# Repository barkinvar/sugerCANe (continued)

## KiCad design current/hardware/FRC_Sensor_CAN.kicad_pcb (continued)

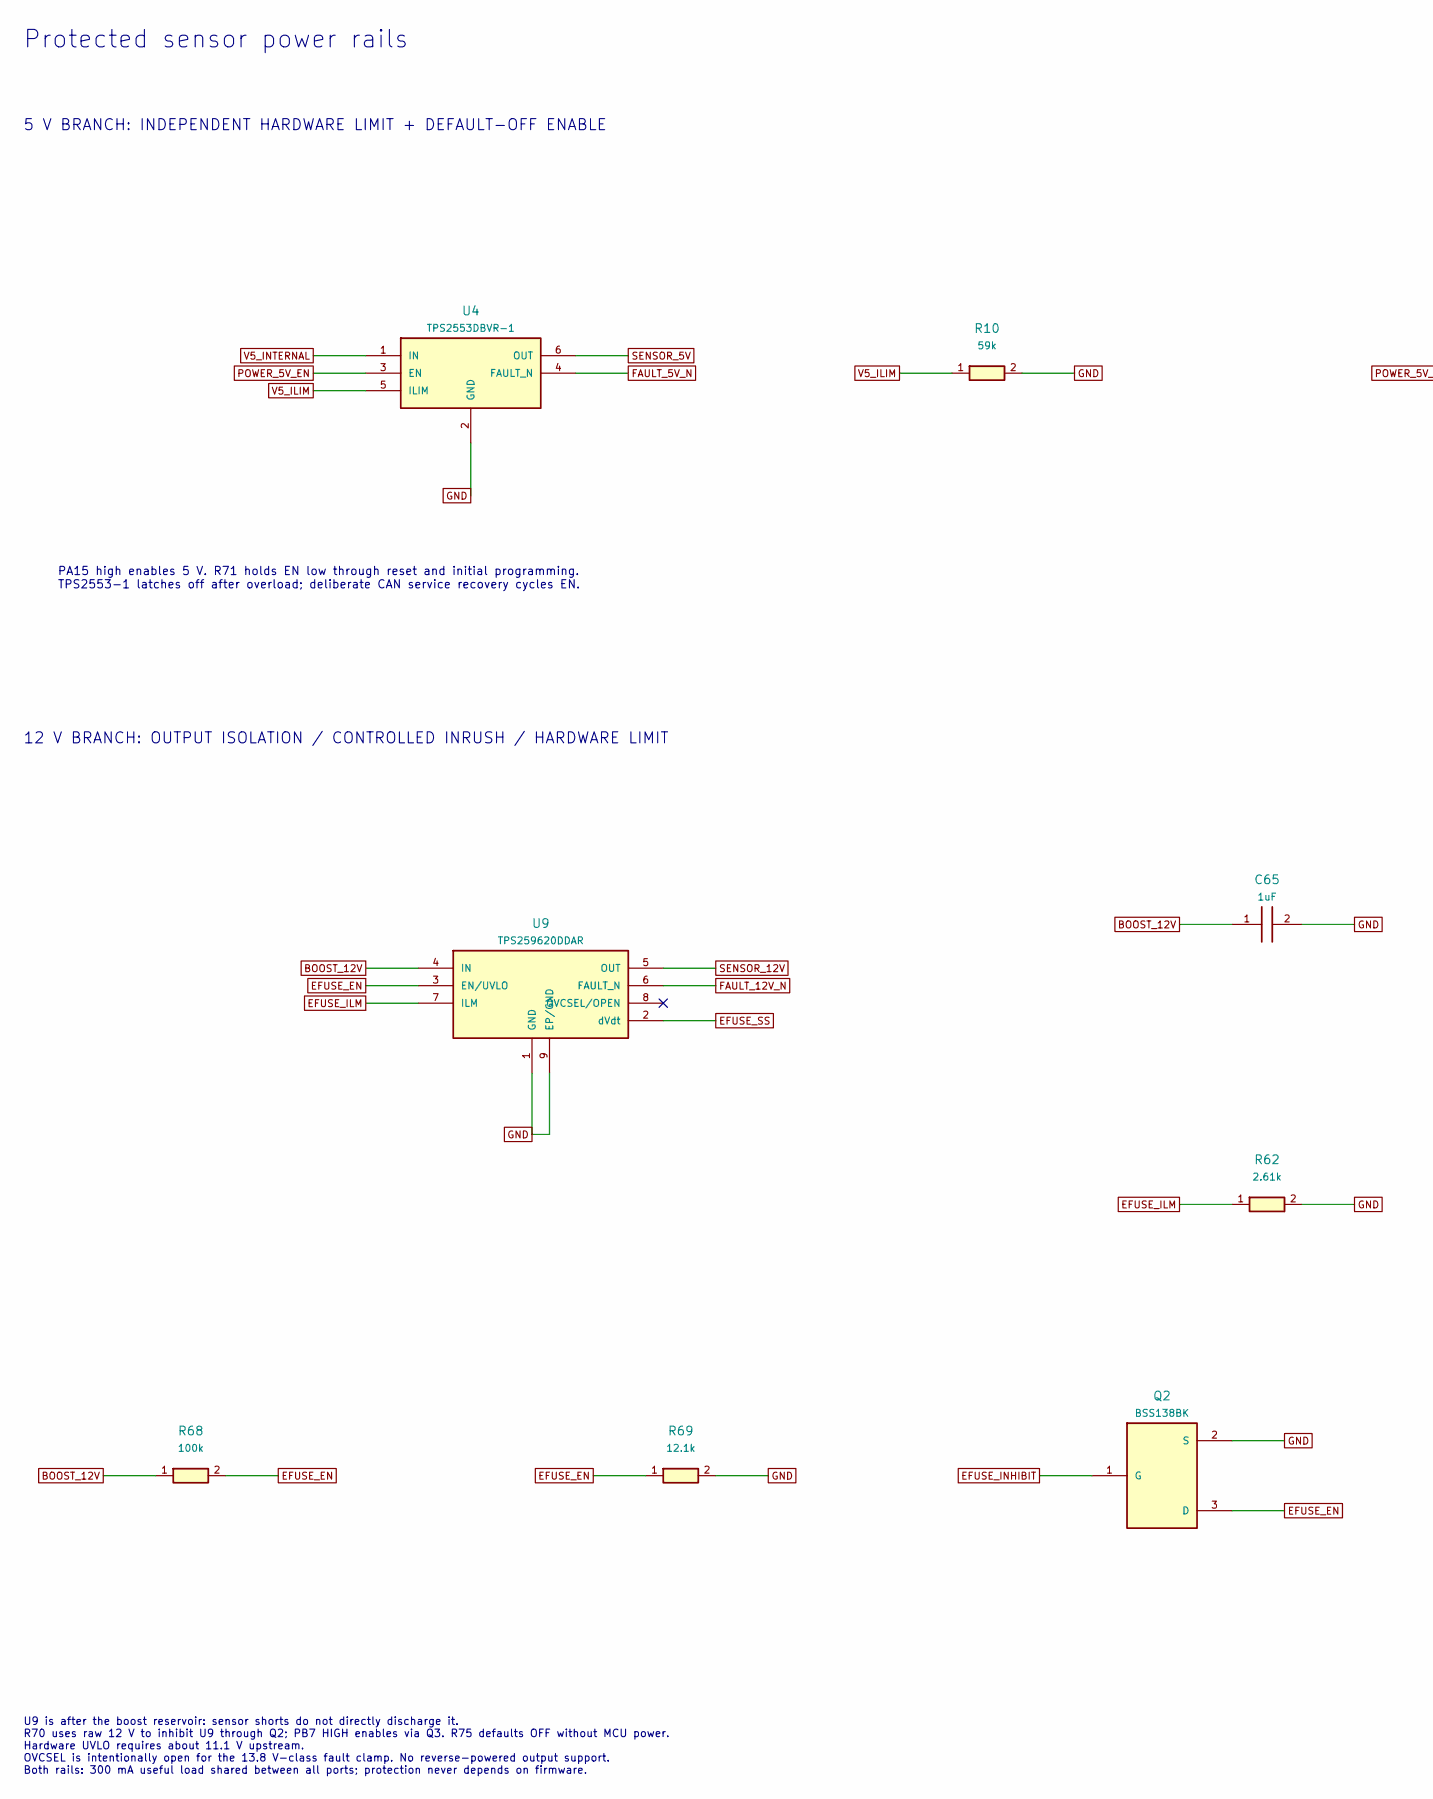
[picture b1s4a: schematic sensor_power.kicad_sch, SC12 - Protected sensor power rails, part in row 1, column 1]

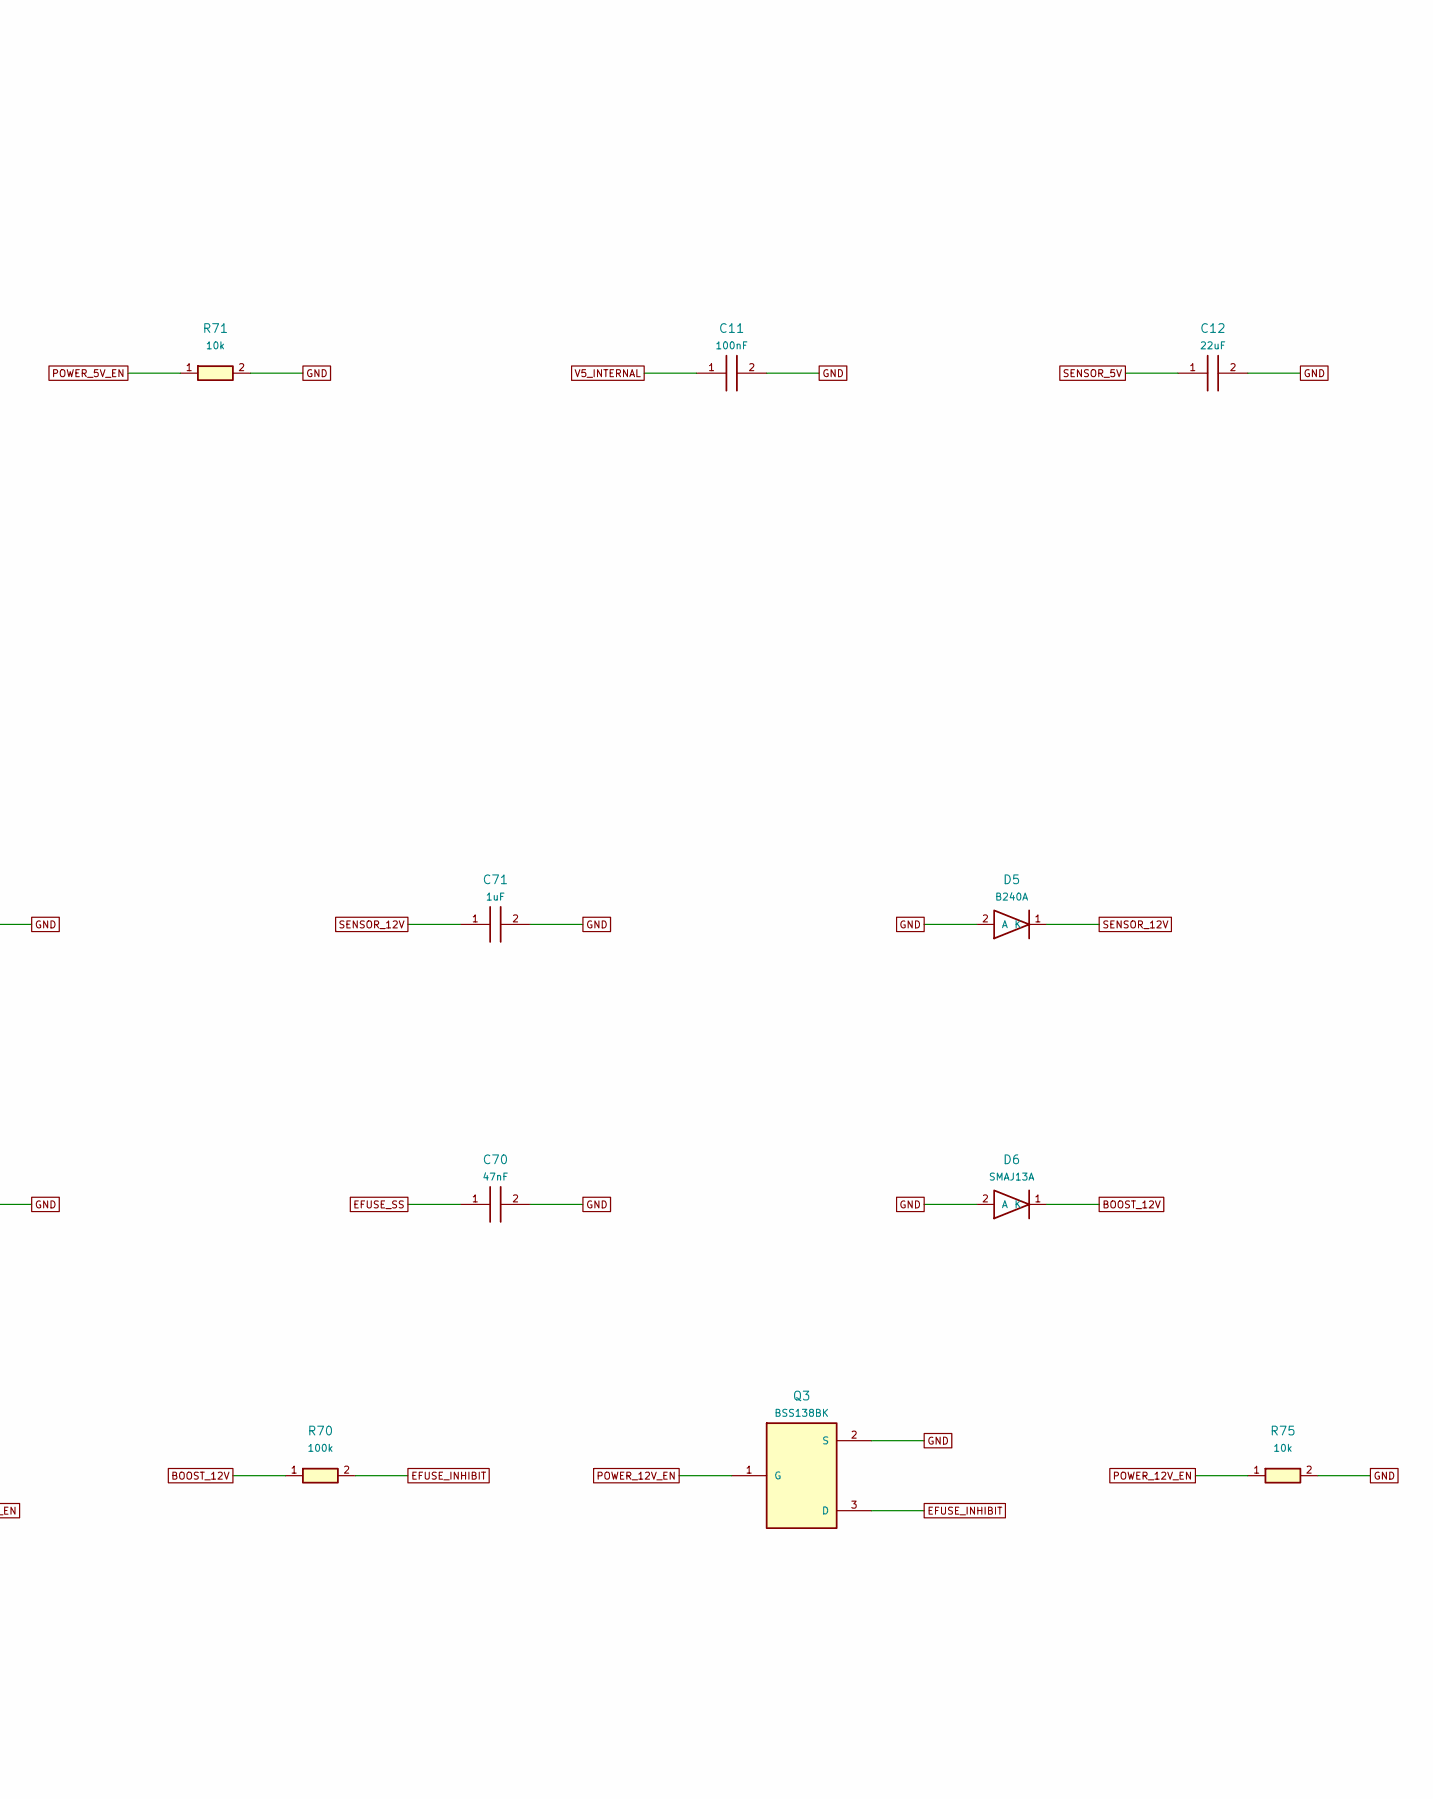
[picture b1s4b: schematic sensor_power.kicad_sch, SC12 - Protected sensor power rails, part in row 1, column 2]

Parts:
C11: 100nF; C_0805_2012Metric; MPN CL21B104KCFNNNE
C12: 22uF; C_1206_3216Metric; MPN CL31A226KAHNNNE
C65, C71: 1uF; C_0805_2012Metric; MPN CL21B105KBFNNNE
C70: 47nF; C_0805_2012Metric; MPN CL21B473KBCNNNC
D5: B240A; D_SMA; MPN B240A-13-F
D6: SMAJ13A; D_SMA; MPN SMAJ13A-13-F
Q2, Q3: BSS138BK; SOT-23; MPN BSS138BK,215
R10: 59k; R_0805_2012Metric; MPN 0805W8F5902T5E
R62: 2.61k; R_0805_2012Metric; MPN RC0805FR-072K61L
R68: 100k; R_0805_2012Metric; MPN RT0805BRD07100KL
R69: 12.1k; R_0805_2012Metric; MPN RT0805BRD0712K1L
R70: 100k; R_0805_2012Metric; MPN 0805W8F1003T5E
R71, R75: 10k; R_0805_2012Metric; MPN 0805W8F1002T5E
U4: TPS2553DBVR-1; SOT-23-6; MPN TPS2553DBVR-1
U9: TPS259620DDAR; TPS2596_DDA8; MPN TPS259620DDAR

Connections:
BOOST_12V: C65.1, D6.1 (K), R68.1, R70.1, U9.4 (IN); also elsewhere on the board
EFUSE_EN: Q2.3 (D), R68.2, R69.1, U9.3 (EN/UVLO)
EFUSE_ILM: R62.1, U9.7 (ILM)
EFUSE_INHIBIT: Q2.1 (G), Q3.3 (D), R70.2
EFUSE_SS: C70.1, U9.2 (dVdt)
FAULT_5V_N: U4.4 (FAULT_N); also elsewhere on the board
FAULT_12V_N: U9.6 (FAULT_N); also elsewhere on the board
GND: C11.2, C12.2, C65.2, C70.2, C71.2, D5.2 (A), D6.2 (A), Q2.2 (S), Q3.2 (S), R10.2, R62.2, R69.2, R71.2, R75.2, U4.2 (GND), U9.1 (GND), U9.9 (EP/GND); also elsewhere on the board
POWER_5V_EN: R71.1, U4.3 (EN); also elsewhere on the board
POWER_12V_EN: Q3.1 (G), R75.1; also elsewhere on the board
SENSOR_5V: C12.1, U4.6 (OUT); also elsewhere on the board
SENSOR_12V: C71.1, D5.1 (K), U9.5 (OUT); also elsewhere on the board
V5_ILIM: R10.1, U4.5 (ILIM)
V5_INTERNAL: C11.1, U4.1 (IN); also elsewhere on the board

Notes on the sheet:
Protected sensor power rails
5 V BRANCH: INDEPENDENT HARDWARE LIMIT + DEFAULT-OFF ENABLE
PA15 high enables 5 V. R71 holds EN low through reset and initial programming. TPS2553-1 latches off after overload; deliberate CAN service recovery cycles EN.
12 V BRANCH: OUTPUT ISOLATION / CONTROLLED INRUSH / HARDWARE LIMIT
U9 is after the boost reservoir: sensor shorts do not directly discharge it. R70 uses raw 12 V to inhibit U9 through Q2; PB7 HIGH enables via Q3. R75 defaults OFF without MCU power. Hardware UVLO requires about 11.1 V upstream. OVCSEL is intentionally open for the 13.8 V-class fault clamp. No rever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

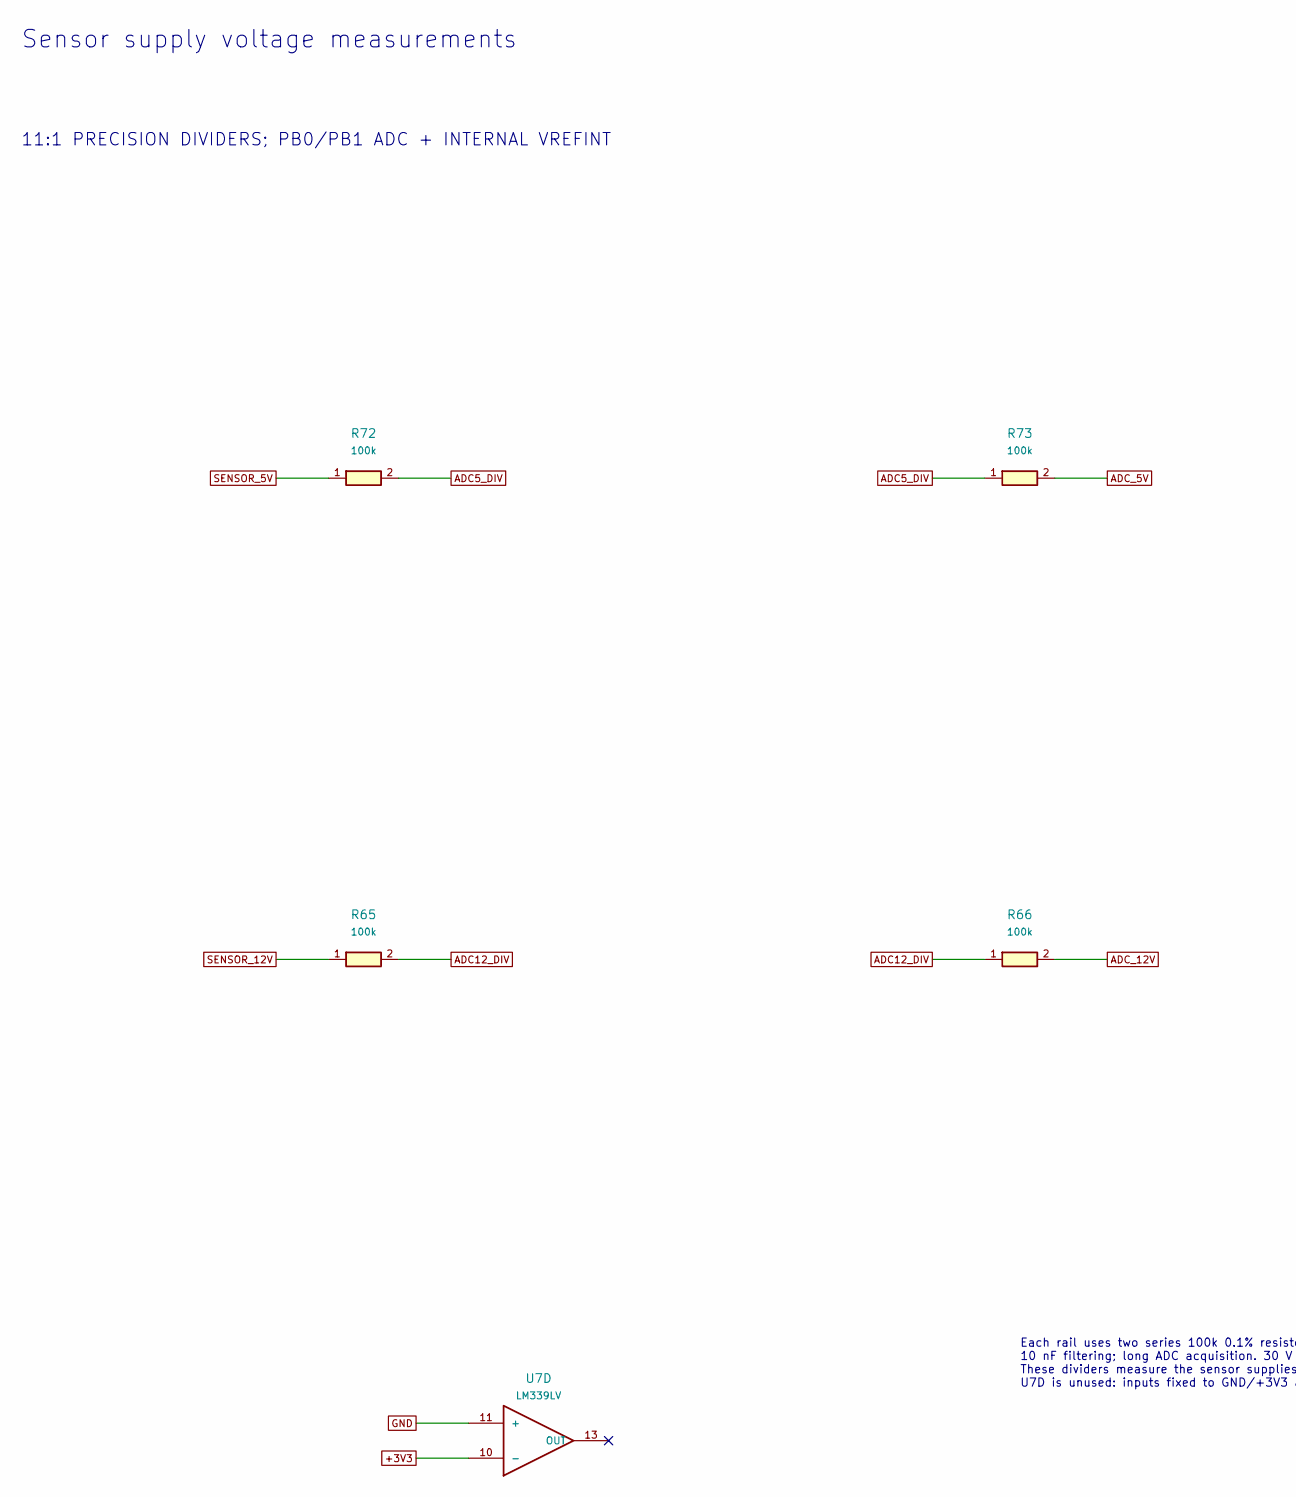
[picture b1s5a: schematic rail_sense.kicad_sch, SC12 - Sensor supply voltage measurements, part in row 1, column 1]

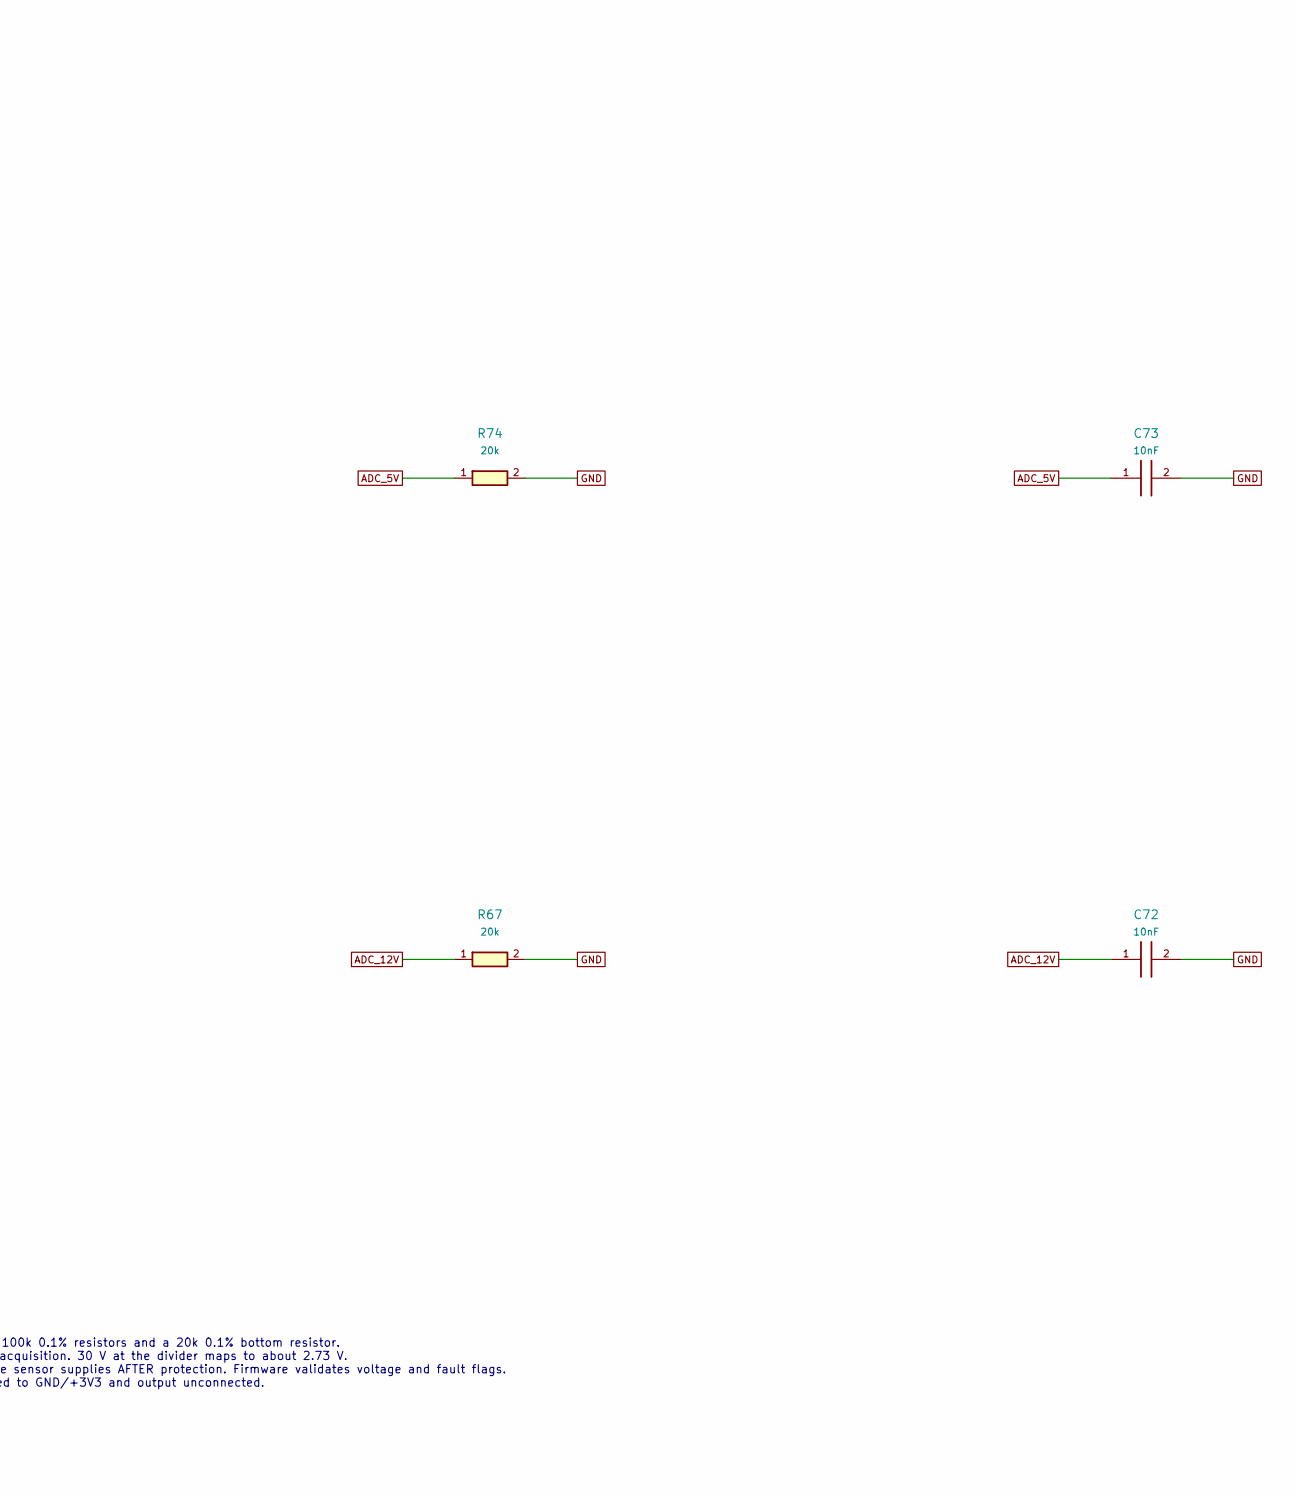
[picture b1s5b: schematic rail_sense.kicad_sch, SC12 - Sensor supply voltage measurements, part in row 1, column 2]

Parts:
C72, C73: 10nF; C_0805_2012Metric; MPN CL21B103KBANNNC
R65, R66, R72, R73: 100k; R_0805_2012Metric; MPN RT0805BRD07100KL
R67, R74: 20k; R_0805_2012Metric; MPN RT0805BRD0720KL
U7: LM339LV; SOIC-14_3.9x8.7mm_P1.27mm; MPN LM339LVDR

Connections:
+3V3: U7.10 (-); also elsewhere on the board
ADC5_DIV: R72.2, R73.1
ADC12_DIV: R65.2, R66.1
ADC_5V: C73.1, R73.2, R74.1; also elsewhere on the board
ADC_12V: C72.1, R66.2, R67.1; also elsewhere on the board
GND: C72.2, C73.2, R67.2, R74.2, U7.11 (+); also elsewhere on the board
SENSOR_5V: R72.1; also elsewhere on the board
SENSOR_12V: R65.1; also elsewhere on the board

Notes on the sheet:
Sensor supply voltage measurements
11:1 PRECISION DIVIDERS; PB0/PB1 ADC + INTERNAL VREFINT
Each rail uses two series 100k 0.1% resistors and a 20k 0.1% bottom resistor. 10 nF filtering; long ADC acquisition. 30 V at the divider maps to about 2.73 V. These dividers measure the sensor supplies AFTER protection. Firmware validates voltage and fault flags. U7D is unused: inputs fixed to GND/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

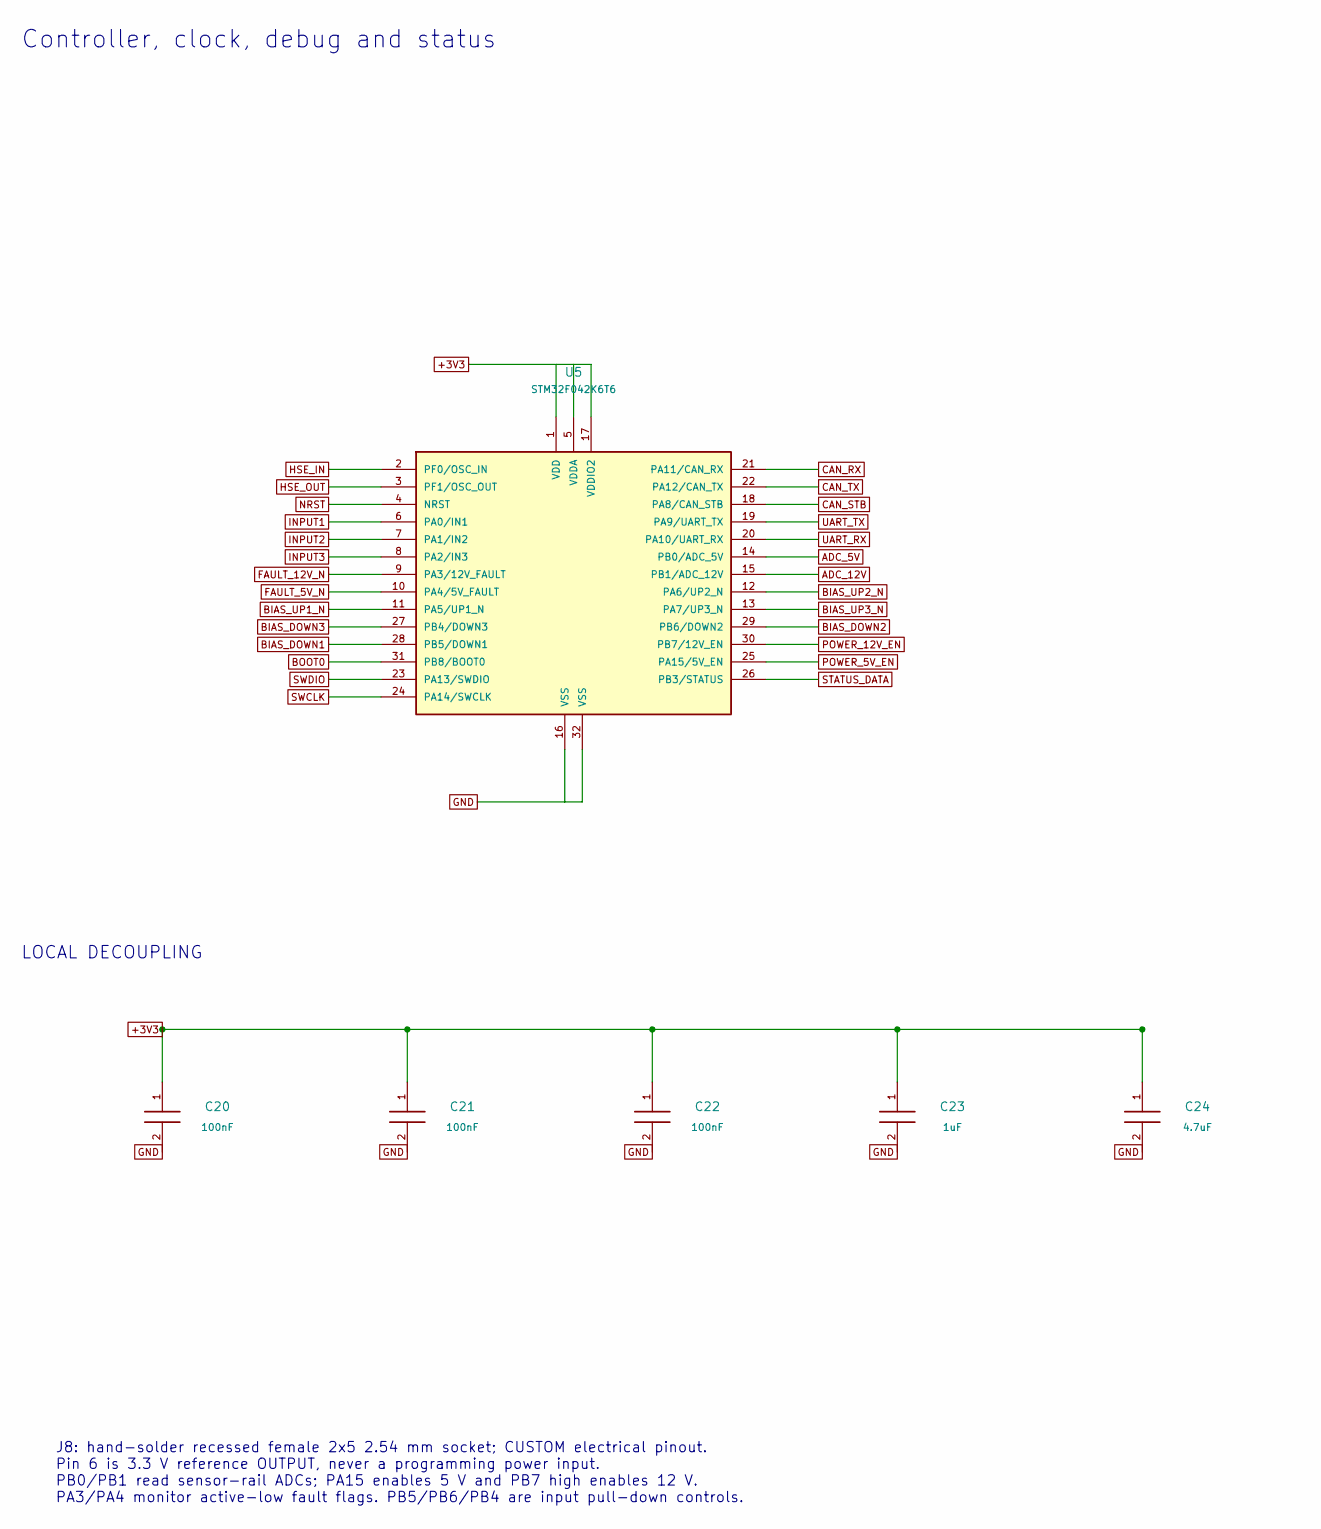
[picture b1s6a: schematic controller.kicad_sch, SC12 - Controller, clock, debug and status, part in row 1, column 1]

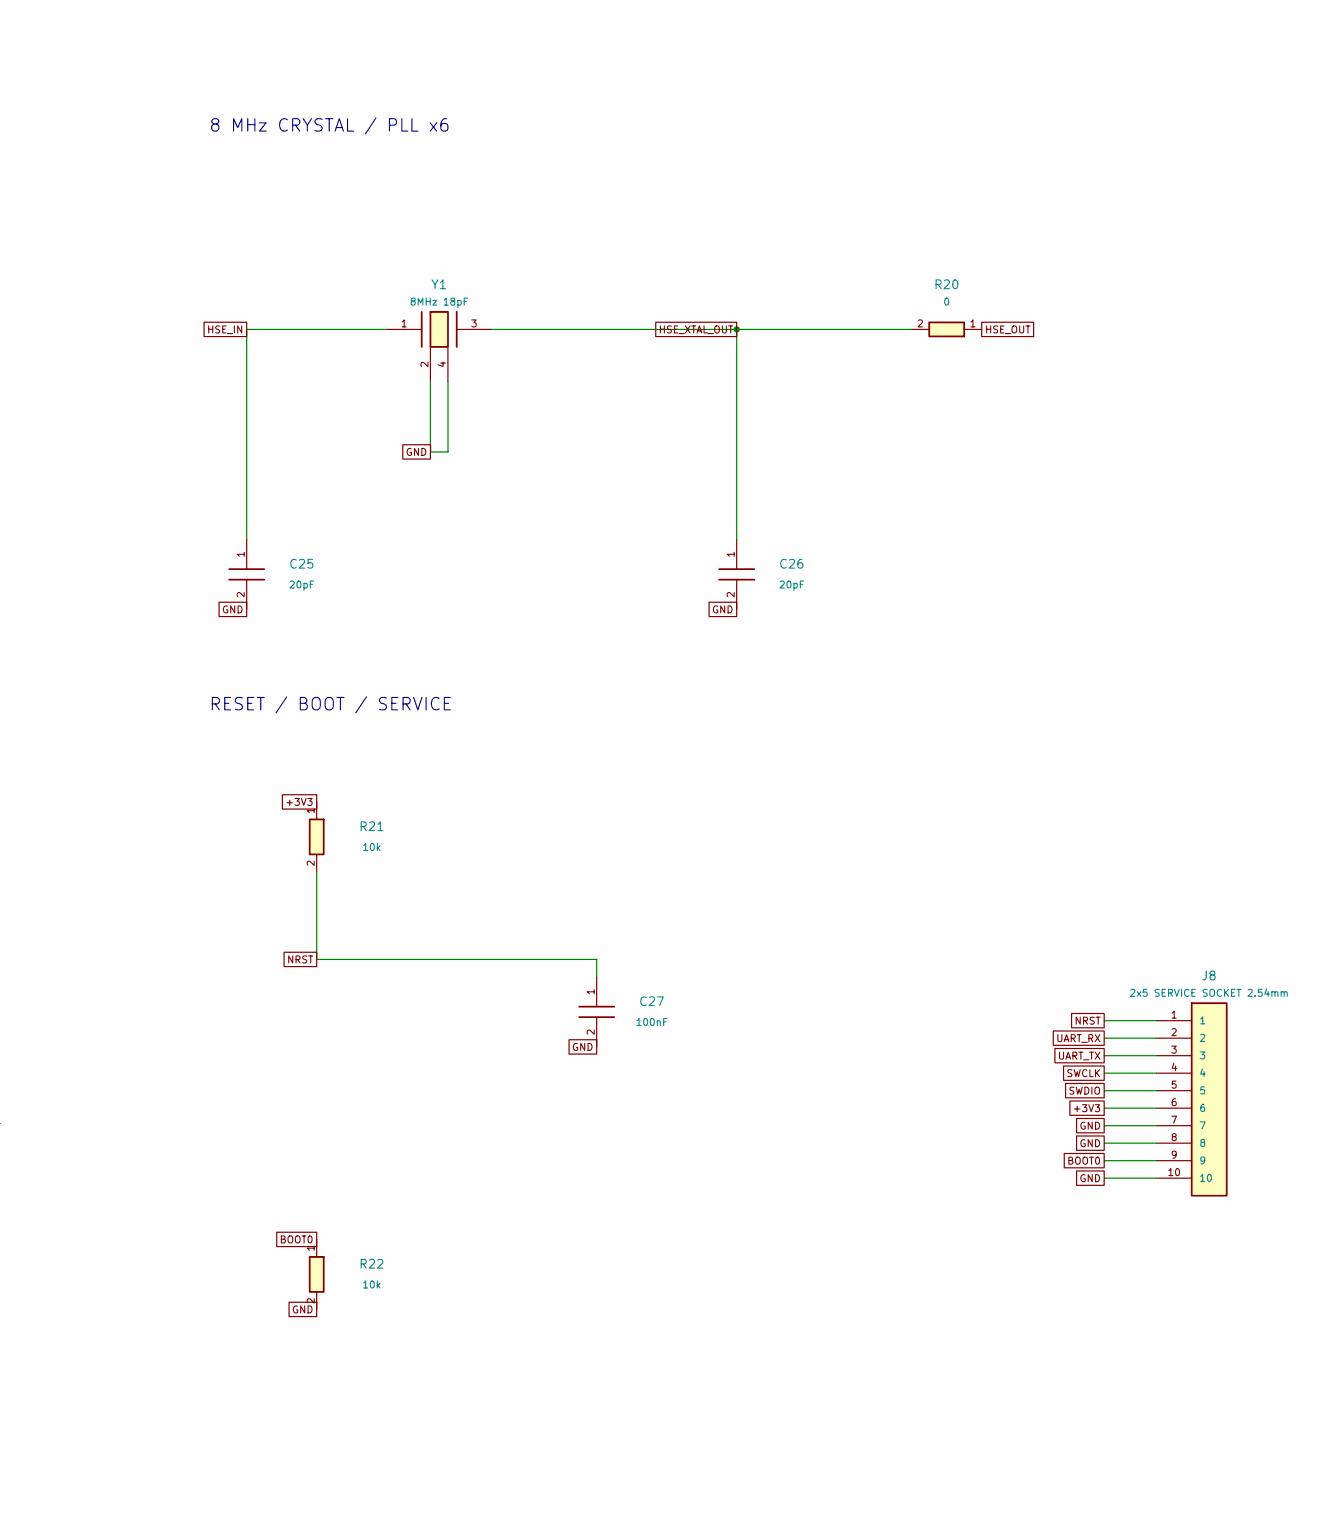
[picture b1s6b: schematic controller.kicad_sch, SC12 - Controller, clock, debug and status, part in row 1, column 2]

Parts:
C20, C21, C22, C27: 100nF; C_0805_2012Metric; MPN CL21B104KCFNNNE
C23: 1uF; C_0805_2012Metric; MPN CL21B105KBFNNNE
C24: 4.7uF; C_0805_2012Metric; MPN CL21B475KAFNNNE
C25, C26: 20pF; C_0805_2012Metric; MPN CC0805JRNPO9BN200
J8: 2x5 SERVICE SOCKET 2.54mm; Service_2x05_P2.54mm; MPN PM254V-12-10P-H85
R20: 0; R_0805_2012Metric; MPN RC0805JR-070RL
R21, R22: 10k; R_0805_2012Metric; MPN 0805W8F1002T5E
U5: STM32F042K6T6; LQFP-32_7x7mm_P0.8mm; MPN STM32F042K6T6
Y1: 8MHz 18pF; Abracon_ABM3B_5.0x3.2mm; MPN ABM3B-8.000MHZ-B2-T

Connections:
+3V3: C20.1, C21.1, C22.1, C23.1, C24.1, J8.6, R21.1, U5.1 (VDD), U5.5 (VDDA), U5.17 (VDDIO2); also elsewhere on the board
ADC_5V: U5.14 (PB0/ADC_5V); also elsewhere on the board
ADC_12V: U5.15 (PB1/ADC_12V); also elsewhere on the board
BIAS_DOWN1: U5.28 (PB5/DOWN1); also elsewhere on the board
BIAS_DOWN2: U5.29 (PB6/DOWN2); also elsewhere on the board
BIAS_DOWN3: U5.27 (PB4/DOWN3); also elsewhere on the board
BIAS_UP1_N: U5.11 (PA5/UP1_N); also elsewhere on the board
BIAS_UP2_N: U5.12 (PA6/UP2_N); also elsewhere on the board
BIAS_UP3_N: U5.13 (PA7/UP3_N); also elsewhere on the board
BOOT0: J8.9, R22.1, U5.31 (PB8/BOOT0)
CAN_RX: U5.21 (PA11/CAN_RX); also elsewhere on the board
CAN_STB: U5.18 (PA8/CAN_STB); also elsewhere on the board
CAN_TX: U5.22 (PA12/CAN_TX); also elsewhere on the board
FAULT_5V_N: U5.10 (PA4/5V_FAULT); also elsewhere on the board
FAULT_12V_N: U5.9 (PA3/12V_FAULT); also elsewhere on the board
GND: C20.2, C21.2, C22.2, C23.2, C24.2, C25.2, C26.2, C27.2, J8.7, J8.8, J8.10, R22.2, U5.16 (VSS), U5.32 (VSS), Y1.2, Y1.4; also elsewhere on the board
HSE_IN: C25.1, U5.2 (PF0/OSC_IN), Y1.1
HSE_OUT: R20.1, U5.3 (PF1/OSC_OUT)
HSE_XTAL_OUT: C26.1, R20.2, Y1.3
INPUT1: U5.6 (PA0/IN1); also elsewhere on the board
INPUT2: U5.7 (PA1/IN2); also elsewhere on the board
INPUT3: U5.8 (PA2/IN3); also elsewhere on the board
NRST: C27.1, J8.1, R21.2, U5.4 (NRST)
POWER_5V_EN: U5.25 (PA15/5V_EN); also elsewhere on the board
POWER_12V_EN: U5.30 (PB7/12V_EN); also elsewhere on the board
STATUS_DATA: U5.26 (PB3/STATUS); also elsewhere on the board
SWCLK: J8.4, U5.24 (PA14/SWCLK)
SWDIO: J8.5, U5.23 (PA13/SWDIO)
UART_RX: J8.2, U5.20 (PA10/UART_RX)
UART_TX: J8.3, U5.19 (PA9/UART_TX)

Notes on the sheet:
Controller, clock, debug and status
8 MHz CRYSTAL / PLL x6
RESET / BOOT / SERVICE
LOCAL DECOUPLING
J8: hand-solder recessed female 2x5 2.54 mm socket; CUSTOM electrical pinout. Pin 6 is 3.3 V reference OUTPUT, never a programming power input. PB0/PB1 read sensor-rail ADCs; PA15 enables 5 V and PB7 high enables 12 V. PA3/PA4 monitor active-low fault flags. PB5/PB6/PB4 are input pull-down controls.

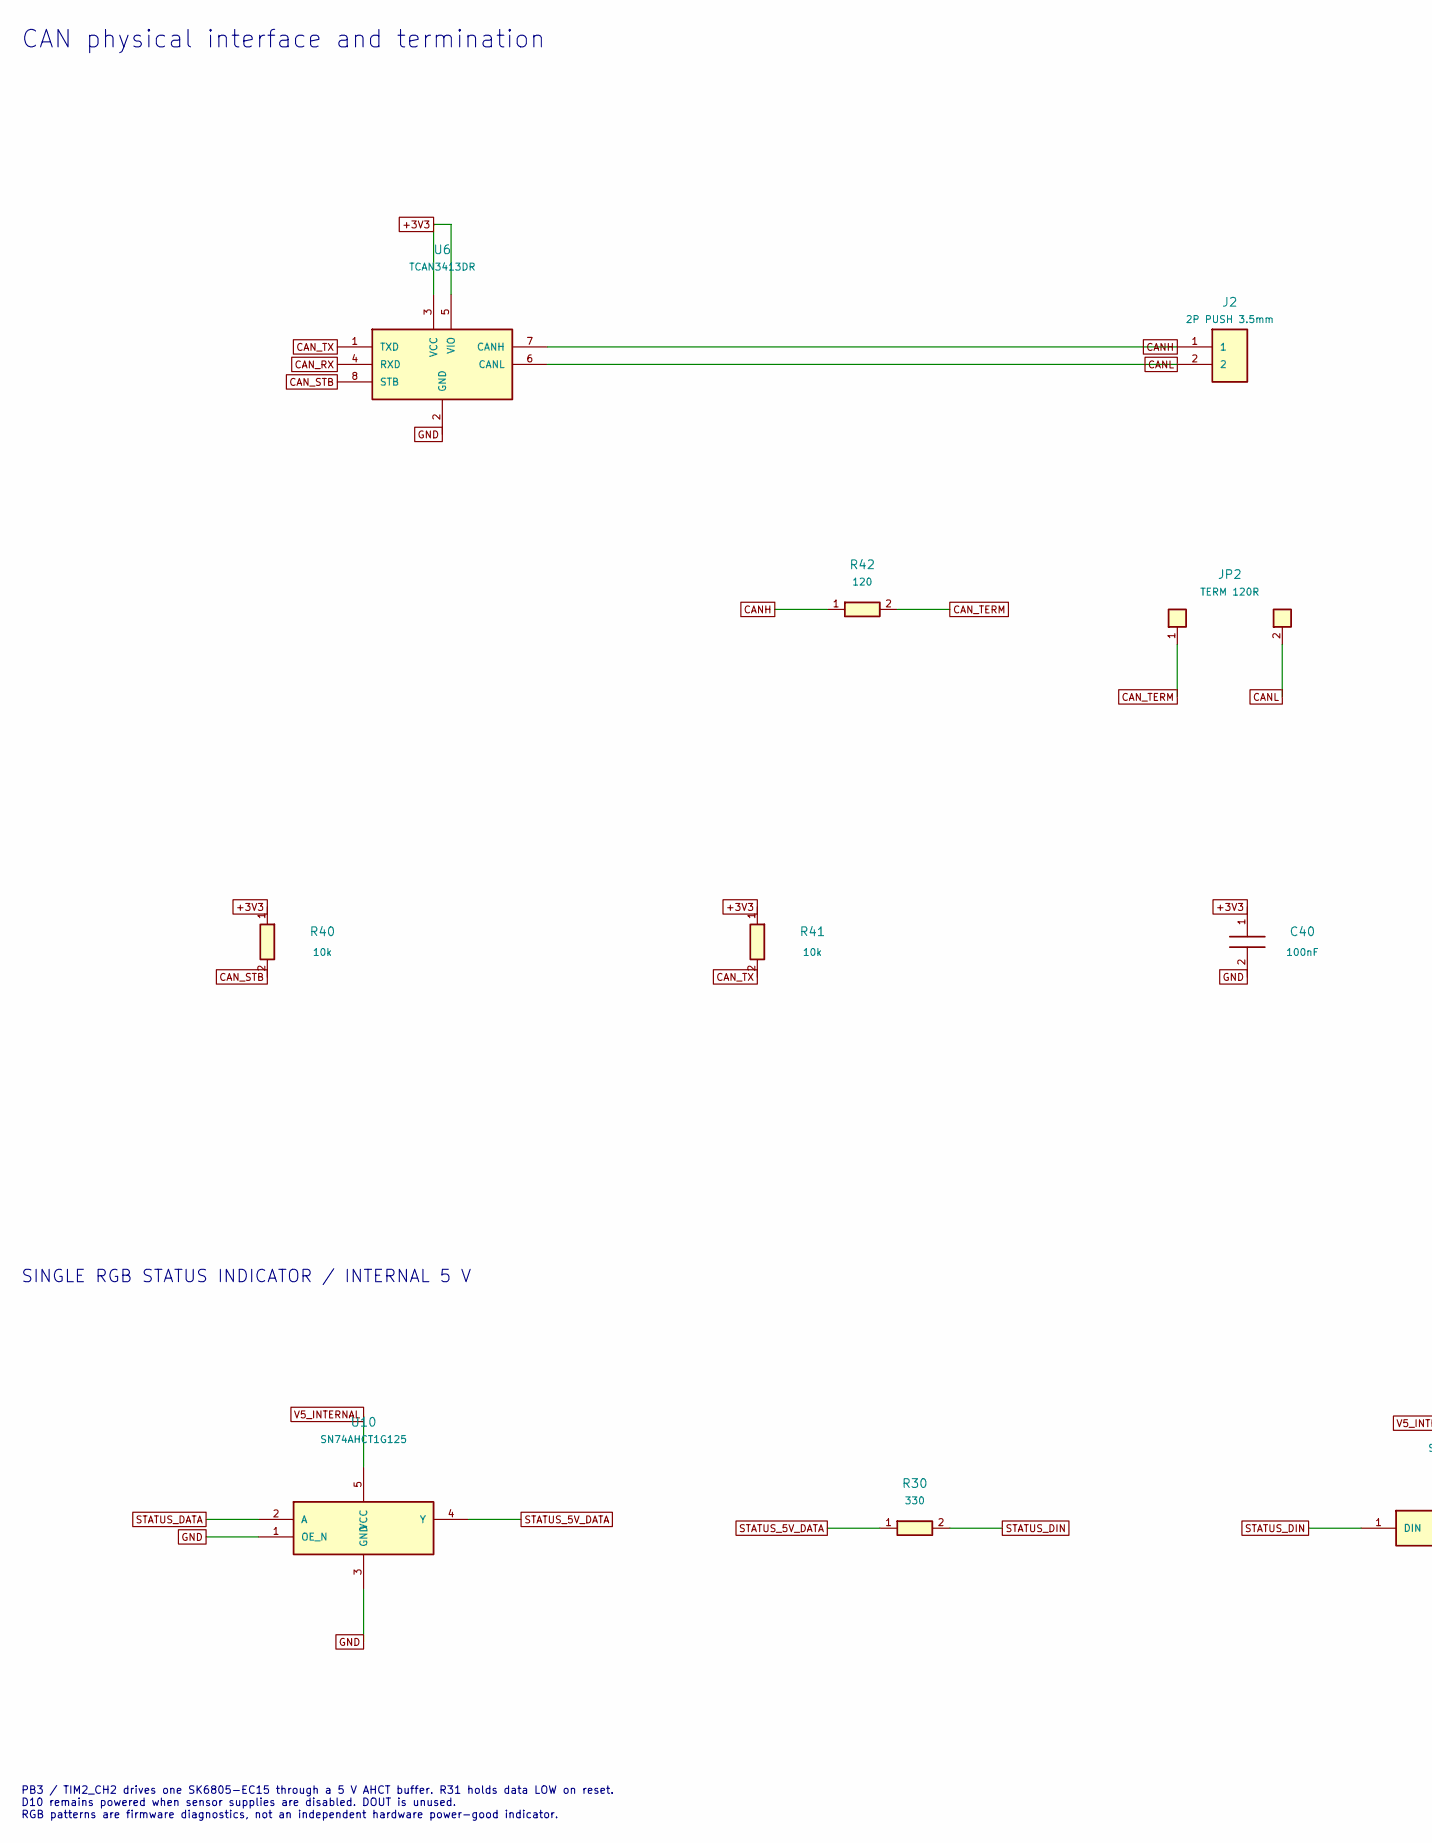
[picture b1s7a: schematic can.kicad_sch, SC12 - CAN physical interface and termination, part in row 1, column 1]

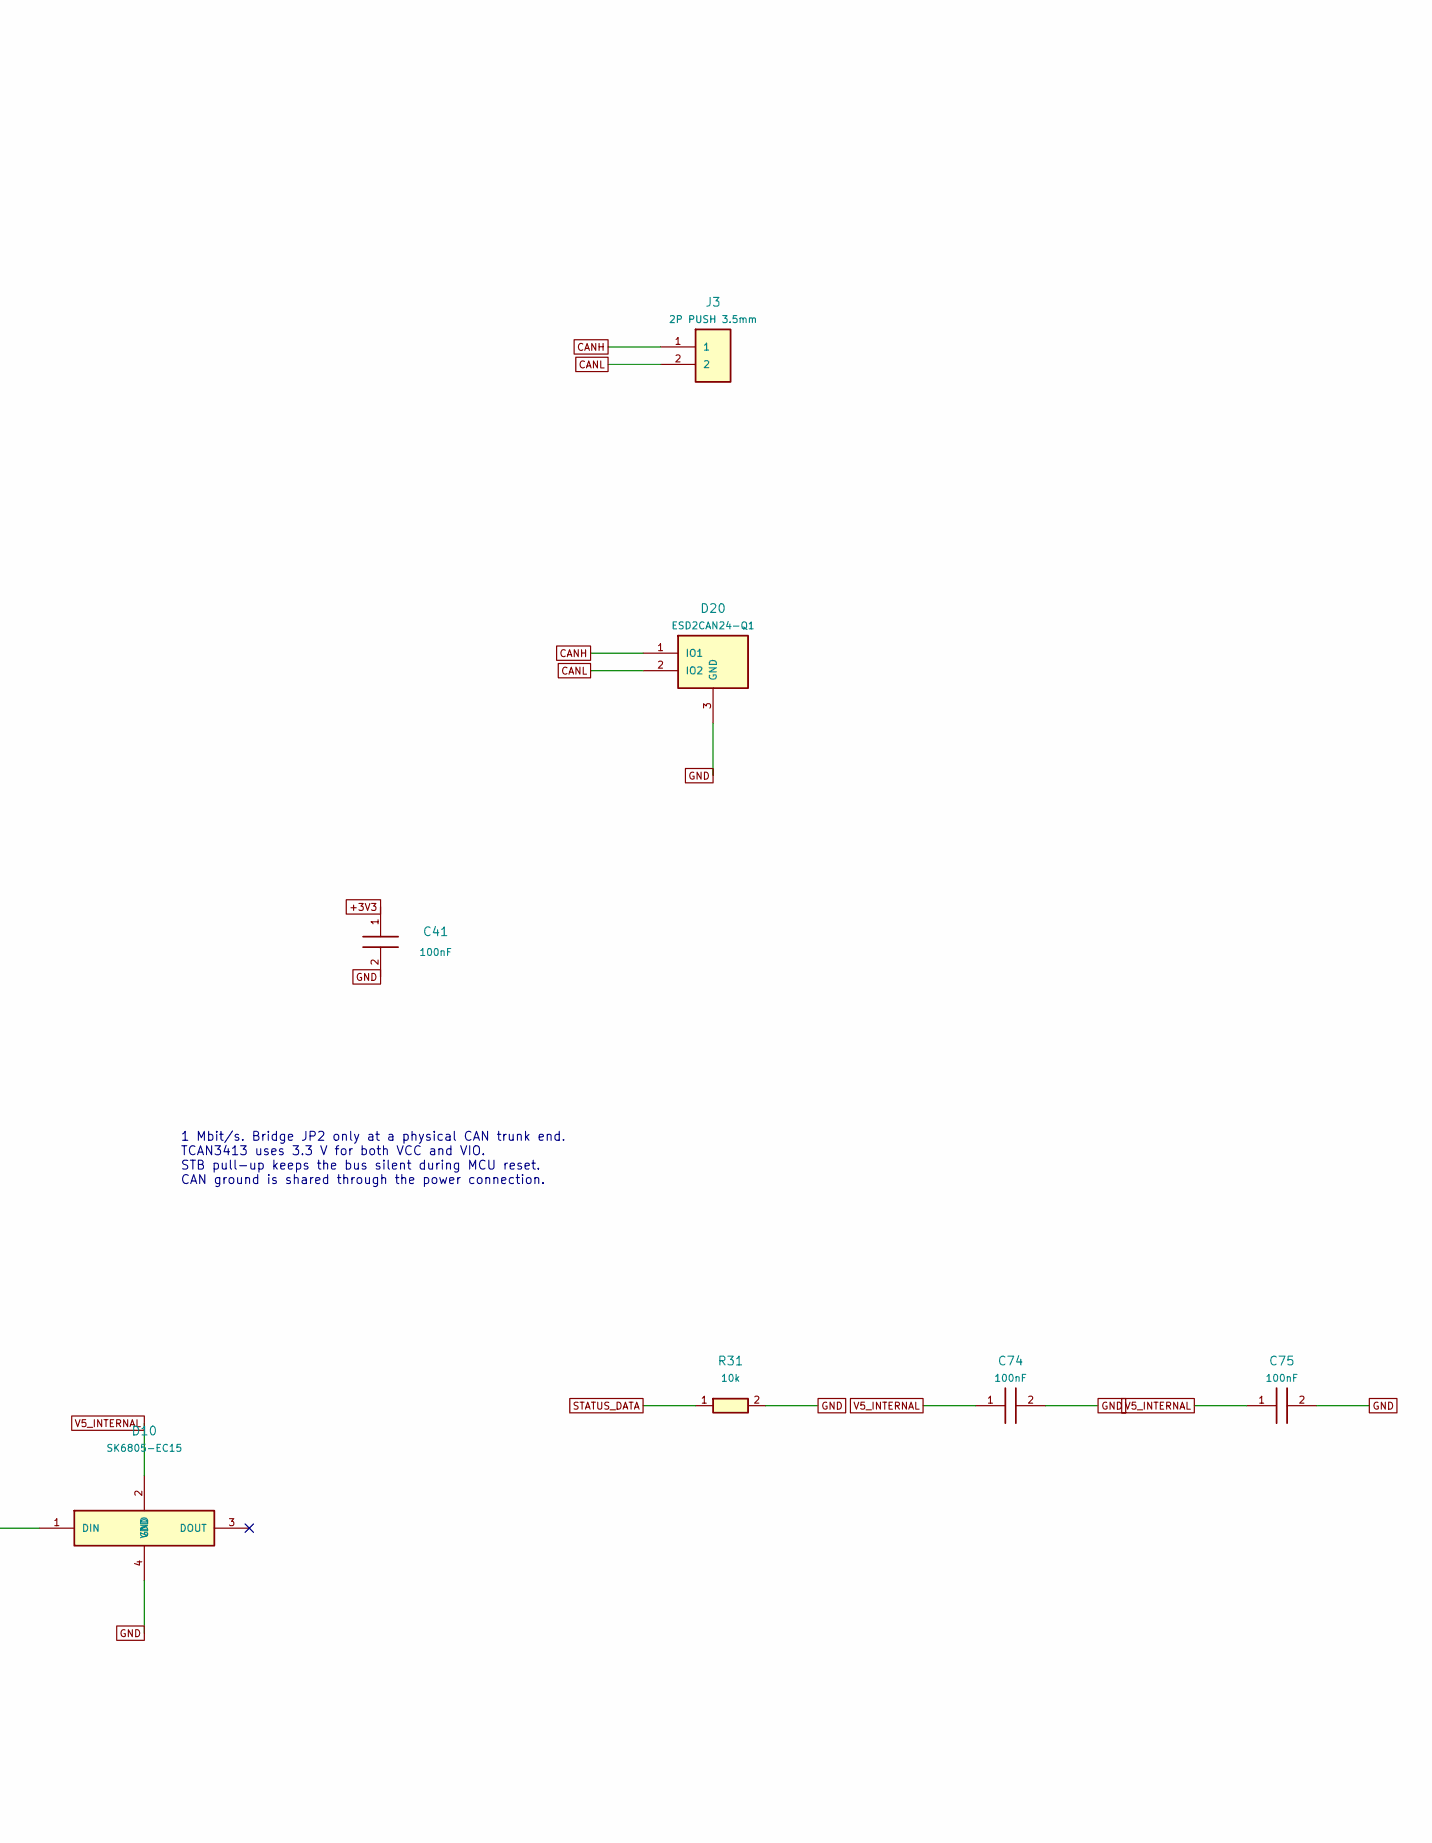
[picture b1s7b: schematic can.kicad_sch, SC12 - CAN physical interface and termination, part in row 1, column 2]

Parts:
C40, C41, C74, C75: 100nF; C_0805_2012Metric; MPN CL21B104KCFNNNE
D10: SK6805-EC15; LED_SK6805_EC15; MPN SK6805-EC15
D20: ESD2CAN24-Q1; SOT-23; MPN ESD2CAN24DBZRQ1
J2, J3: 2P PUSH 3.5mm; Weidmuller_LSF_90_2P; MPN 1824420000
JP2: TERM 120R; SolderSelector_2
R30: 330; R_0805_2012Metric; MPN 0805W8F3300T5E
R31, R40, R41: 10k; R_0805_2012Metric; MPN 0805W8F1002T5E
R42: 120; R_1206_3216Metric; MPN 1206W4F1200T5E
U6: TCAN3413DR; SOIC-8_3.9x4.9mm_P1.27mm; MPN TCAN3413DR
U10: SN74AHCT1G125; SOT-23-5; MPN SN74AHCT1G125DBVR

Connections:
+3V3: C40.1, C41.1, R40.1, R41.1, U6.3 (VCC), U6.5 (VIO); also elsewhere on the board
CANH: D20.1 (IO1), J2.1, J3.1, R42.1, U6.7 (CANH)
CANL: D20.2 (IO2), J2.2, J3.2, JP2.2, U6.6 (CANL)
CAN_RX: U6.4 (RXD); also elsewhere on the board
CAN_STB: R40.2, U6.8 (STB); also elsewhere on the board
CAN_TERM: JP2.1, R42.2
CAN_TX: R41.2, U6.1 (TXD); also elsewhere on the board
GND: C40.2, C41.2, C74.2, C75.2, D10.4 (GND), D20.3 (GND), R31.2, U6.2 (GND), U10.1 (OE_N), U10.3 (GND); also elsewhere on the board
STATUS_5V_DATA: R30.1, U10.4 (Y)
STATUS_DATA: R31.1, U10.2 (A); also elsewhere on the board
STATUS_DIN: D10.1 (DIN), R30.2
V5_INTERNAL: C74.1, C75.1, D10.2 (VDD), U10.5 (VCC); also elsewhere on the board

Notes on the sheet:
CAN physical interface and termination
1 Mbit/s. Bridge JP2 only at a physical CAN trunk end. TCAN3413 uses 3.3 V for both VCC and VIO. STB pull-up keeps the bus silent during MCU reset. CAN ground is shared through the power connection.
SINGLE RGB STATUS INDICATOR / INTERNAL 5 V
PB3 / TIM2_CH2 drives one SK6805-EC15 through a 5 V AHCT buffer. R31 holds data LOW on reset. D10 remains powered when sensor supplies are disabled. DOUT is unused. RGB patterns are firmware diagnostics, not an independent hardware power-good indicator.
